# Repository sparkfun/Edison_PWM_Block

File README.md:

SparkFun Edison PWM Block
==================================================

[*SparkFun Edison PWM Block(DEV-13042)*](https://www.sparkfun.com/products/13042)

This card adds eight channels of PWM control to the Edison's I<sup>2</sup>C bus. While the PWM output can be used for any generic PWM application, it is specifically intended to provide drive control for up to eight standard hobby-type servo motors. To that end, it has an independent input for supply voltage for the servos above the normal range of the Edison, and 8 connections that support the most common pinout of hobby servo motors.

The PCA9685 provides open-collector or push-pull output capabilities; as the intended target is servo motors, the board has a pull-up resistor to the independently connected servo supply voltage. The PCA9685 has an independent clock that can be operated at 50Hz, for servo control; at that frequency, the 12-bit resolution of the device provides approximately 200 steps of resolution for a servo motor.

The PCA9685 can be used as an open collector current driver for LEDs up to 25mA as well. Six solder jumpers allow the user to attach up to 63 of these cards to a single Edison, or to adjust the address of the PCA9685 to avoid collision with other addresses on the bus.

Repository Contents
-------------------
* **/Hardware** - All Eagle design files (.brd, .sch)
* **/Production** - Test bed files and production panel files

License Information
-------------------
The hardware is released under [Creative Commons ShareAlike 4.0 International](https://creativecommons.org/licenses/by-sa/4.0/).
The code is beerware; if you see me (or any other SparkFun employee) at the local, and you've found our code helpful, please buy us a round!

Distributed as-is; no warranty is given.

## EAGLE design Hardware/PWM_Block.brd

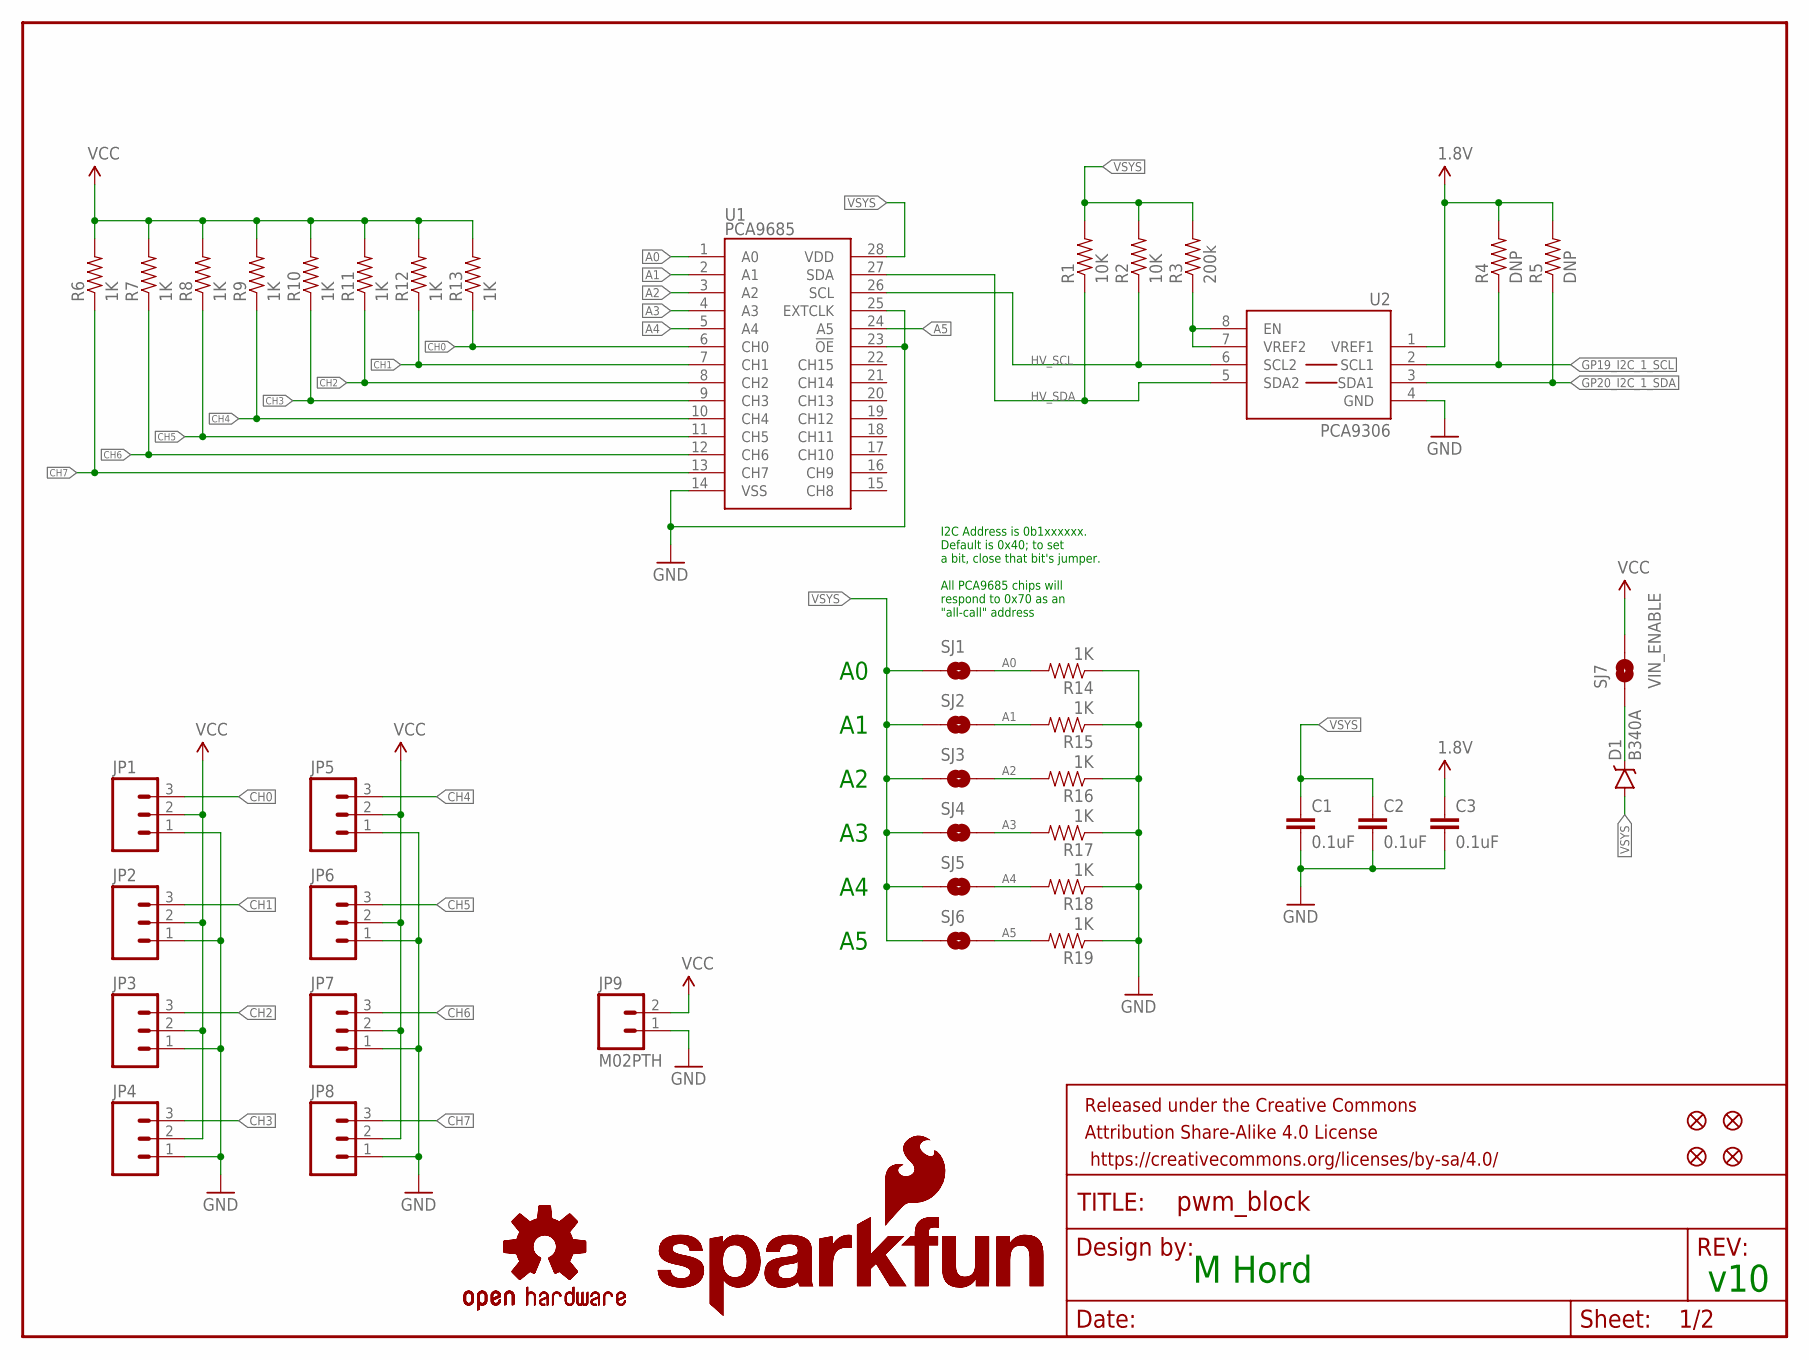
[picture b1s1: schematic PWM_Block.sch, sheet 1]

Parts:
C1, C2, C3: 0.1uF; 0603-CAP
D1: B340A; SMA-DIODE
FID1, FID2, FID3, FID4: FIDUCIAL1X2; FIDUCIAL-1X2
FRAME1: FRAME-LETTER; CREATIVE_COMMONS
JP1, JP2, JP3, JP4, JP5, JP6, JP7, JP8: M03PTH; 1X03
JP9: M02PTH; 1X02
LOGO1, LOGO3: SFE_LOGO_NAME_FLAME.1_INCH; SFE_LOGO_NAME_FLAME_.1
LOGO2, LOGO4: OSHW-LOGOS; OSHW-LOGO-S
R1, R2: 10K; 0603-RES
R3: 200k; 0603-RES
R4, R5: DNP; 0603-RES
R6, R7, R8, R9, R10, R11, R12, R13, R14, R15, R16, R17, R18, R19: 1K; 0603-RES
SJ1, SJ2, SJ3, SJ4, SJ5, SJ6: JUMPER-PAD-2-NOYES_SILK; PAD-JUMPER-2-NO_YES_SILK
SJ7: VIN_ENABLE; PAD-JUMPER-2-NO_YES_SILK
U1: PCA9685; TSSOP-28_4MM
U2: PCA9306; PCA9306DC-1:1

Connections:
1.8V: C3.1, R4.2, R5.2, U2.1 (VREF1); also elsewhere on the board
A0: R14.2, SJ1.2, U1.1 (A0)
A1: R15.2, SJ2.2, U1.2 (A1)
A2: R16.2, SJ3.2, U1.3 (A2)
A3: R17.2, SJ4.2, U1.4 (A3)
A4: R18.2, SJ5.2, U1.5 (A4)
A5: R19.2, SJ6.2, U1.24 (A5)
CH0: JP1.3, R13.1, U1.6 (CH0)
CH1: JP2.3, R12.1, U1.7 (CH1)
CH2: JP3.3, R11.1, U1.8 (CH2)
CH3: JP4.3, R10.1, U1.9 (CH3)
CH4: JP5.3, R9.1, U1.10 (CH4)
CH5: JP6.3, R8.1, U1.11 (CH5)
CH6: JP7.3, R7.1, U1.12 (CH6)
CH7: JP8.3, R6.1, U1.13 (CH7)
GND: C1.2, C2.2, C3.2, JP1.1, JP2.1, JP3.1, JP4.1, JP5.1, JP6.1, JP7.1, JP8.1, JP9.1, R14.1, R15.1, R16.1, R17.1, R18.1, R19.1, U1.14 (VSS), U1.23 (!OE), U1.25 (EXTCLK), U2.4 (GND); also elsewhere on the board
GP19_I2C_1_SCL: R4.1, U2.2 (SCL1); also elsewhere on the board
GP20_I2C_1_SDA: R5.1, U2.3 (SDA1); also elsewhere on the board
HV_SCL: R2.1, U1.26 (SCL), U2.6 (SCL2)
HV_SDA: R1.1, U1.27 (SDA), U2.5 (SDA2)
unnamed: R3.1, U2.7 (VREF2), U2.8 (EN)
unnamed: D1.C, SJ7.1
VCC: JP1.2, JP2.2, JP3.2, JP4.2, JP5.2, JP6.2, JP7.2, JP8.2, JP9.2, R6.2, R7.2, R8.2, R9.2, R10.2, R11.2, R12.2, R13.2, SJ7.2
VSYS: C1.1, C2.1, D1.A, R1.2, R2.2, R3.2, SJ1.1, SJ2.1, SJ3.1, SJ4.1, SJ5.1, SJ6.1, U1.28 (VDD); also elsewhere on the board

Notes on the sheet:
M Hord
v10
I2C Address is 0b1xxxxxx. Default is 0x40; to set a bit, close that bit's jumper. All PCA9685 chips will respond to 0x70 as an "all-call" address

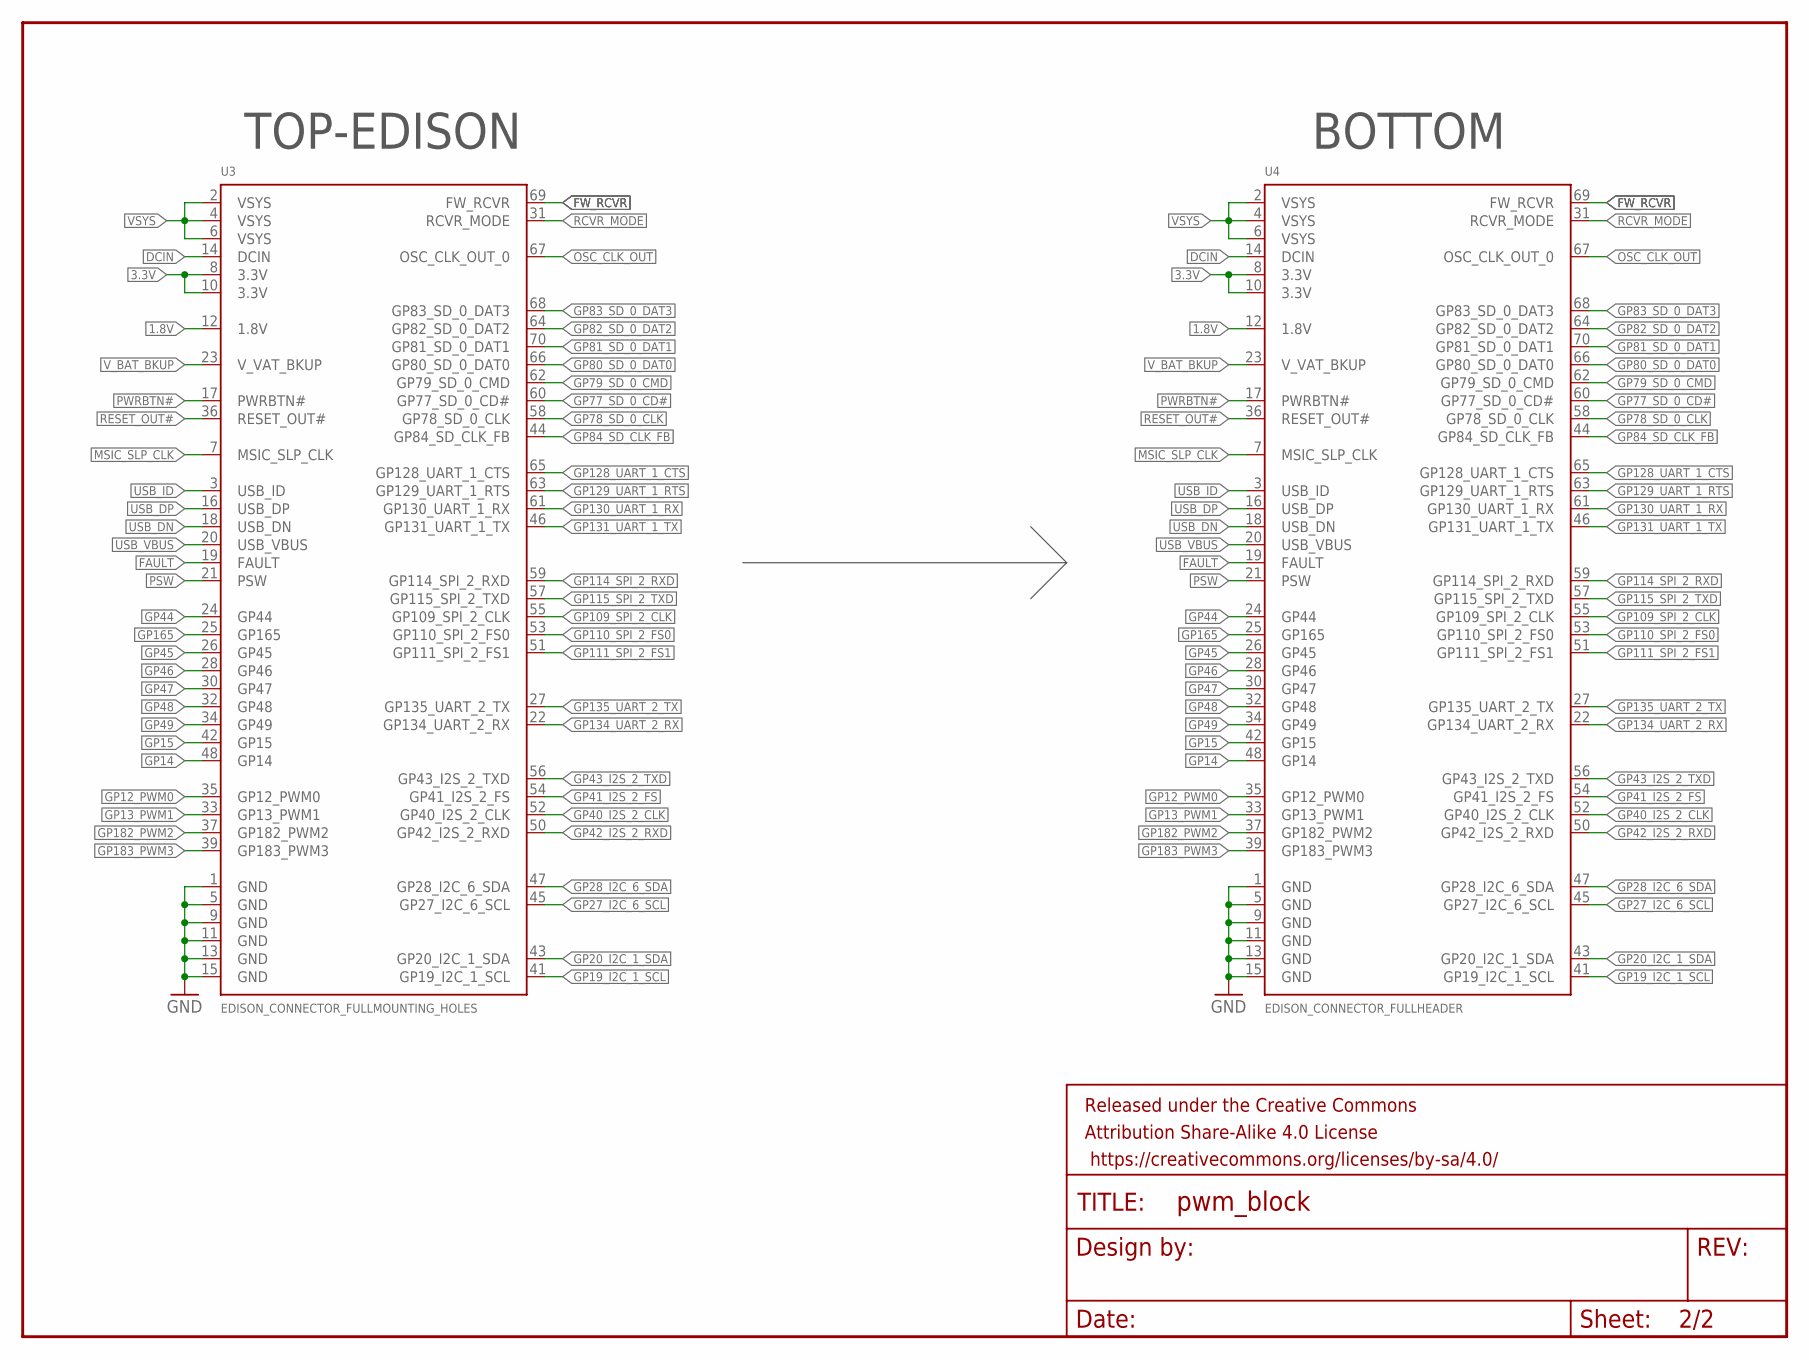
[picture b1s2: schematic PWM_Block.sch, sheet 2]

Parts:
FRAME2: FRAME-LETTER; CREATIVE_COMMONS
U3: EDISON_CONNECTOR_FULLMOUNTING_HOLES; EDISON_DAUGHTER
U4: EDISON_CONNECTOR_FULLHEADER; DF40C-70DP-0.4(51)

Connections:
1.8V: U3.12 (1.8V), U4.12 (1.8V); also elsewhere on the board
3.3V: U3.8 (3.3V), U3.10 (3.3V), U4.8 (3.3V), U4.10 (3.3V)
DCIN: U3.14 (DCIN), U4.14 (DCIN)
FAULT: U3.19 (FAULT), U4.19 (FAULT)
FW_RCVR: U3.69 (FW_RCVR), U4.69 (FW_RCVR)
GND: U3.1 (GND), U3.5 (GND), U3.9 (GND), U3.11 (GND), U3.13 (GND), U3.15 (GND), U4.1 (GND), U4.5 (GND), U4.9 (GND), U4.11 (GND), U4.13 (GND), U4.15 (GND); also elsewhere on the board
GP12_PWM0: U3.35 (GP12_PWM0), U4.35 (GP12_PWM0)
GP13_PWM1: U3.33 (GP13_PWM1), U4.33 (GP13_PWM1)
GP14: U3.48 (GP14), U4.48 (GP14)
GP15: U3.42 (GP15), U4.42 (GP15)
GP19_I2C_1_SCL: U3.41 (GP19_I2C_1_SCL), U4.41 (GP19_I2C_1_SCL); also elsewhere on the board
GP20_I2C_1_SDA: U3.43 (GP20_I2C_1_SDA), U4.43 (GP20_I2C_1_SDA); also elsewhere on the board
GP27_I2C_6_SCL: U3.45 (GP27_I2C_6_SCL), U4.45 (GP27_I2C_6_SCL)
GP28_I2C_6_SDA: U3.47 (GP28_I2C_6_SDA), U4.47 (GP28_I2C_6_SDA)
GP40_I2S_2_CLK: U3.52 (GP40_I2S_2_CLK), U4.52 (GP40_I2S_2_CLK)
GP41_I2S_2_FS: U3.54 (GP41_I2S_2_FS), U4.54 (GP41_I2S_2_FS)
GP42_I2S_2_RXD: U3.50 (GP42_I2S_2_RXD), U4.50 (GP42_I2S_2_RXD)
GP43_I2S_2_TXD: U3.56 (GP43_I2S_2_TXD), U4.56 (GP43_I2S_2_TXD)
GP44: U3.24 (GP44), U4.24 (GP44)
GP45: U3.26 (GP45), U4.26 (GP45)
GP46: U3.28 (GP46), U4.28 (GP46)
GP47: U3.30 (GP47), U4.30 (GP47)
GP48: U3.32 (GP48), U4.32 (GP48)
GP49: U3.34 (GP49), U4.34 (GP49)
GP77_SD_0_CD#: U3.60 (GP77_SD_0_CD#), U4.60 (GP77_SD_0_CD#)
GP78_SD_0_CLK: U3.58 (GP78_SD_0_CLK), U4.58 (GP78_SD_0_CLK)
GP79_SD_0_CMD: U3.62 (GP79_SD_0_CMD), U4.62 (GP79_SD_0_CMD)
GP80_SD_0_DAT0: U3.66 (GP80_SD_0_DAT0), U4.66 (GP80_SD_0_DAT0)
GP81_SD_0_DAT1: U3.70 (GP81_SD_0_DAT1), U4.70 (GP81_SD_0_DAT1)
GP82_SD_0_DAT2: U3.64 (GP82_SD_0_DAT2), U4.64 (GP82_SD_0_DAT2)
GP83_SD_0_DAT3: U3.68 (GP83_SD_0_DAT3), U4.68 (GP83_SD_0_DAT3)
GP84_SD_CLK_FB: U3.44 (GP84_SD_CLK_FB), U4.44 (GP84_SD_CLK_FB)
GP109_SPI_2_CLK: U3.55 (GP109_SPI_2_CLK), U4.55 (GP109_SPI_2_CLK)
GP110_SPI_2_FS0: U3.53 (GP110_SPI_2_FS0), U4.53 (GP110_SPI_2_FS0)
GP111_SPI_2_FS1: U3.51 (GP111_SPI_2_FS1), U4.51 (GP111_SPI_2_FS1)
GP114_SPI_2_RXD: U3.59 (GP114_SPI_2_RXD), U4.59 (GP114_SPI_2_RXD)
GP115_SPI_2_TXD: U3.57 (GP115_SPI_2_TXD), U4.57 (GP115_SPI_2_TXD)
GP128_UART_1_CTS: U3.65 (GP128_UART_1_CTS), U4.65 (GP128_UART_1_CTS)
GP129_UART_1_RTS: U3.63 (GP129_UART_1_RTS), U4.63 (GP129_UART_1_RTS)
GP130_UART_1_RX: U3.61 (GP130_UART_1_RX), U4.61 (GP130_UART_1_RX)
GP131_UART_1_TX: U3.46 (GP131_UART_1_TX), U4.46 (GP131_UART_1_TX)
GP134_UART_2_RX: U3.22 (GP134_UART_2_RX), U4.22 (GP134_UART_2_RX)
GP135_UART_2_TX: U3.27 (GP135_UART_2_TX), U4.27 (GP135_UART_2_TX)
GP165: U3.25 (GP165), U4.25 (GP165)
GP182_PWM2: U3.37 (GP182_PWM2), U4.37 (GP182_PWM2)
GP183_PWM3: U3.39 (GP183_PWM3), U4.39 (GP183_PWM3)
MSIC_SLP_CLK: U3.7 (MSIC_SLP_CLK), U4.7 (MSIC_SLP_CLK)
OSC_CLK_OUT: U3.67 (OSC_CLK_OUT_0), U4.67 (OSC_CLK_OUT_0)
PSW: U3.21 (PSW), U4.21 (PSW)
PWRBTN#: U3.17 (PWRBTN#), U4.17 (PWRBTN#)
RCVR_MODE: U3.31 (RCVR_MODE), U4.31 (RCVR_MODE)
RESET_OUT#: U3.36 (RESET_OUT#), U4.36 (RESET_OUT#)
USB_DN: U3.18 (USB_DN), U4.18 (USB_DN)
USB_DP: U3.16 (USB_DP), U4.16 (USB_DP)
USB_ID: U3.3 (USB_ID), U4.3 (USB_ID)
USB_VBUS: U3.20 (USB_VBUS), U4.20 (USB_VBUS)
VSYS: U3.2 (VSYS), U3.4 (VSYS), U3.6 (VSYS), U4.2 (VSYS), U4.4 (VSYS), U4.6 (VSYS); also elsewhere on the board
V_BAT_BKUP: U3.23 (V_VAT_BKUP), U4.23 (V_VAT_BKUP)

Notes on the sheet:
TOP-EDISON
BOTTOM

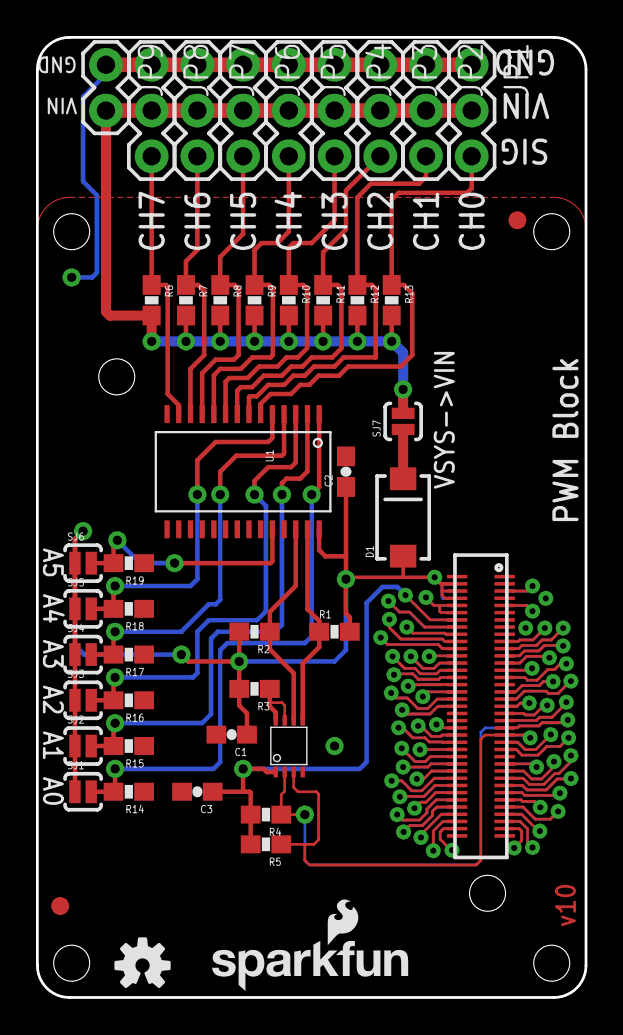
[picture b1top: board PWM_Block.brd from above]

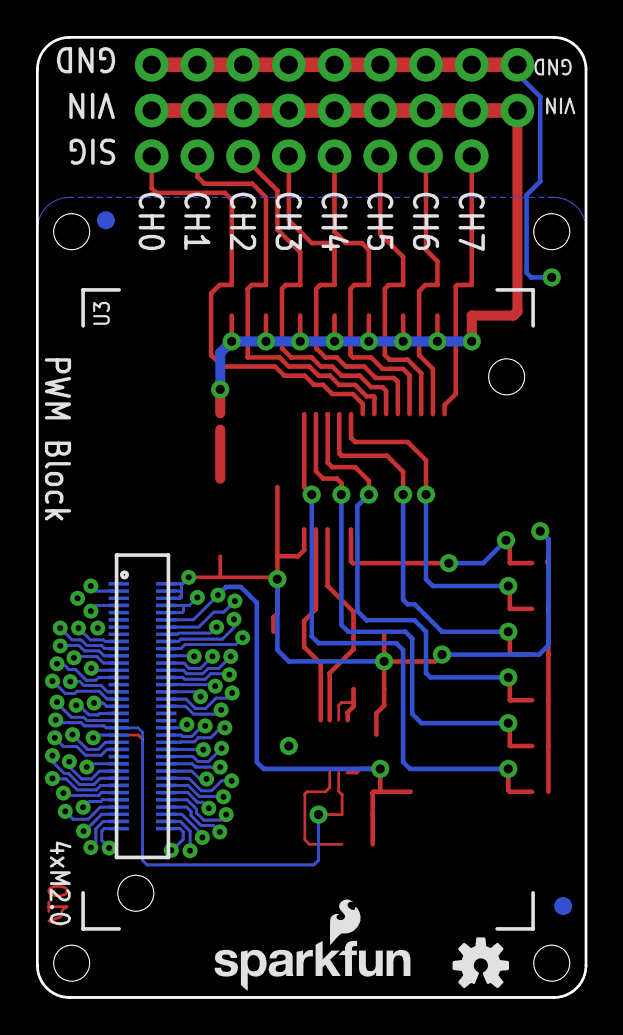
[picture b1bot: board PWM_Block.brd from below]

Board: 2 copper layers, 30.5 x 53.3 mm, 53 parts (6 on the bottom side), 77 nets.

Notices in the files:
parts and their libraries:
SparkFun-Aesthetics: Licensing: Creative Commons ShareAlike 4.0 International - https://creativecommons.org/licenses/by-sa/4.0
SparkFun-Aesthetics: Released under the Creative Commons Attribution Share-Alike 4.0 License
SparkFun-Aesthetics: Released under the Creative Commons
